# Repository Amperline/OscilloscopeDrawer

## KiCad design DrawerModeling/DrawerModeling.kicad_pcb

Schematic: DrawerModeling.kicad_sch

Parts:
B1_a1, B1_a2, B1_b1, B1_b2, B2_a1, B2_a2, B2_b1, B2_b2: Conn_01x01; SolderWirePad_1x01_SMD_1.5x3mm
C1, C2, C3, C5, C6, C7, C10, C13, C14: C; C_Axial_L3.8mm_D2.6mm_P7.50mm_Horizontal
C4: C_Polarized; CP_Radial_D6.3mm_P2.50mm; not fitted
C_G1, C_G2: C; C_0603_1608Metric
C_s1, C_s3, C_s4, C_s8: 100n; C_0603_1608Metric
C_s5, C_s6: 1u; C_0603_1608Metric
C_s7: C; C_0603_1608Metric
ConnProgramator1: Conn_01x04_Pin; PinHeader_1x04_P2.54mm_Vertical
D1: 1N4148; D_DO-35_SOD27_P7.62mm_Horizontal
D5, D6: LED; LED_D5.0mm
J1: Conn_01x05_Pin; PinHeader_1x05_P2.54mm_Vertical
Q1, Q2, Q4, Q5: 2N3904; TO-92_Inline
Q3: 2N3906; TO-92_Inline
R1, R2: 4.7k; R_Axial_DIN0207_L6.3mm_D2.5mm_P10.16mm_Horizontal
R3, R4, R5, R6, R7, R8, R9, R10, R11, R13, R14, R15, R16, R17, R19, R20, R21, R22, R23, R24, R25, R26, R27, R28, R29, R30, R31, R32, R33, R34, R35, R36, R37, R38, R39, R40, R41, R42, R43, R44, R45, R46: R; R_Axial_DIN0207_L6.3mm_D2.5mm_P10.16mm_Horizontal
R18: R_Potentiometer_US; Potentiometer_Alps_RK163_Single_Horizontal
R60: 10k; R_Axial_DIN0207_L6.3mm_D2.5mm_P10.16mm_Horizontal
U1: AD633JRZ-R7; SOIC127P600X175-8N; MPN AD633JRZ-R7; not fitted
U2, U6, U9, U10, U13, U15: TL072; DIP-8_W10.16mm
U3: Arduino_LCD_Shield
U4: TL082_Block; DIP-8_W7.62mm; not fitted
U5: PinHeader_1x20_P2.54mm_Vertical; not fitted
U7: STM32F401CCUx; QFN-48-1EP_7x7mm_P0.5mm_EP5.6x5.6mm
U8, U20: LT1011; SOIC-8_3.9x4.9mm_P1.27mm
U11, U12, U16, U17: TLP222A; TLP127
U14: LM13700; DIP-16_W7.62mm
U18: MCP4725xxx-xCH; SOT-23-6
U19: XC6206PxxxMR; SOT-23-3
UART1: Conn_01x03_Pin; PinHeader_1x03_P2.54mm_Vertical
V3: VPWL; not fitted
Vw_GND1: Conn_01x01; SolderWirePad_1x01_SMD_1.5x3mm
Vw_MC1: Conn_01x01; SolderWirePad_1x01_SMD_1.5x3mm
Vw_Mdltn1: Conn_01x01; SolderWirePad_1x01_SMD_1.5x3mm
Vw_Out1: Conn_01x01; SolderWirePad_1x01_SMD_1.5x3mm
Vw_PWM1: Conn_01x01; SolderWirePad_1x01_SMD_1.5x3mm
Vw_SIN1: Conn_01x01; SolderWirePad_1x01_SMD_1.5x3mm
Vw_SIN+Cnst1: Conn_01x01; SolderWirePad_1x01_SMD_1.5x3mm
Vw_long1: Conn_01x01; SolderWirePad_1x01_SMD_1.5x3mm
Vw_short1: Conn_01x01; SolderWirePad_1x01_SMD_1.5x3mm
Y1: Crystal; Crystal_HC49-U_Vertical

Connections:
/3V3: C_s1.1, C_s3.1, C_s4.1, C_s6.2, ConnProgramator1.4, R33.2, U7.1 (VBAT), U7.9 (VREF+), U7.24 (VDD), U7.36 (VDD), U7.48 (VDD), U19.2 (VO), U20.8 (V+)
/LCD_CS: U3.25 (LCD_CS), U7.19 (PB1)
/LCD_DC: U3.22 (LCD_DS), U7.18 (PB0)
/MISO: U3.27 (MISO), U7.16 (PA6)
/MOSI: U3.26 (MOSI), U7.17 (PA7)
/PWM: Q1.2 (B), R41.1, R42.2, U7.10 (PA0), Vw_PWM1.1
/RX: U7.31 (PA10), UART1.2
/SCL: R1.2, U7.42 (PB6), U18.5 (SCL)
/SCLK: U3.28 (SCLK), U7.15 (PA5)
/SDA: R2.2, U7.43 (PB7), U18.4 (SDA)
/SD_CS: U3.20 (SD_CS), U7.40 (PB4)
/SWCLK: ConnProgramator1.2, U7.37 (PA14)
/SWDIO: ConnProgramator1.3, U7.34 (PA13)
/Signal_drwng: U10.5 (+), U18.1 (VOUT)
/TP_CS: U3.19 (TP_CS), U7.20 (PB2)
/TP_IRQ: U3.18 (TP_IRQ), U7.25 (PB12)
/TX: U7.30 (PA9), UART1.1
/V5: C_s5.2, J1.2, Q2.3 (C), R1.1, R2.1, R26.2, U3.5 (+5V), U3.24 (LCD_BL), U18.3 (VDD), U19.3 (VI)
/V5m: J1.4
/V15: C2.1, C14.1, J1.1, Q4.3 (C), R13.2, R25.2, R35.1, R40.2, R41.2, R44.1, U2.8 (V+), U6.8 (V+), U8.8 (V+), U9.8 (V+), U10.8 (V+), U13.8 (V+), U14.11 (V+), U15.8 (V+)
/V15m: B2_a1.1, B2_a2.1, J1.5, R23.1, U2.4 (V-), U6.4 (V-), U8.4 (V-), U9.4 (V-), U10.4 (V-), U13.4 (V-), U14.6 (V-), U15.4 (V-)
GND: C1.2, C2.2, C3.2, C5.1, C13.2, C14.2, C_G1.1, C_G2.1, C_s1.2, C_s3.2, C_s4.2, C_s5.1, C_s6.1, C_s7.1, C_s8.2, ConnProgramator1.1, J1.3, R6.1, R9.2, R10.1, R16.2, R28.1, R34.2, R36.1, R39.1, R42.1, R43.2, R45.2, R46.1, R60.1, U3.6 (GND), U7.8 (VSSA), U7.23 (VSS), U7.35 (VSS), U7.47 (VSS), U7.49 (VSS), U8.1 (GND), U8.2 (+), U9.3 (+), U11.2, U11.3, U12.2, U13.3 (+), U13.5 (+), U14.3 (+), U15.5 (+), U18.2 (VSS), U19.1 (GND), U20.1 (GND), U20.2 (+), U20.4 (V-), UART1.3, Vw_GND1.1
unnamed: B1_a1.1, D1.1 (K)
unnamed: B1_a2.1, U10.1, U10.2 (-)
unnamed: B1_b1.1, R15.2, R18.1, U11.4
unnamed: B1_b2.1, R19.2, R20.2, U12.4
unnamed: B2_b1.1, D6.1 (K), U17.2
unnamed: B2_b2.1, D5.1 (K), U16.2
unnamed: C7.1, R8.1
unnamed: D1.2 (A), U9.6 (-), U9.7
unnamed: D5.2 (A), D6.2 (A), R9.1
unnamed: Q1.3 (C), R40.1
unnamed: Q1.1 (E), R7.1, R39.2
unnamed: Q2.2 (B), R19.1
unnamed: Q2.1 (E), R21.1
unnamed: Q3.2 (B), R15.1, R20.1
unnamed: Q3.3 (C), R27.1
unnamed: Q3.1 (E), R26.1, R28.2
unnamed: C5.2, Q4.2 (B), R18.2, U12.3
unnamed: Q4.1 (E), Q5.2 (B), R34.1, R35.2, R45.1
unnamed: Q5.3 (C), R44.2
unnamed: Q5.1 (E), R29.1, R43.1
unnamed: R11.2, R24.1, U14.16
unnamed: R16.1, U16.1, U17.1
unnamed: R21.2, U12.1
unnamed: R22.2, U15.7, U16.4
unnamed: R27.2, U11.1
unnamed: R30.2, R31.1, U13.1
unnamed: R37.1, R38.2, U2.1
unnamed: U1.5 (W), U1.6 (+VS)
unnamed: C3.1, R7.2, U2.3 (+)
unnamed: R36.2, R38.1, U2.2 (-)
unnamed: C13.1, R37.2, U2.5 (+)
unnamed: R5.1, U2.6 (-), U2.7
unnamed: U5.B2, V3.1
unnamed: U5.GND, V3.2
unnamed: C1.1, R5.2, U6.3 (+)
unnamed: C6.1, U6.1, U6.2 (-), Vw_SIN+Cnst1.1
unnamed: R8.2, U6.6 (-), U6.7
unnamed: R60.2, U7.44 (BOOT0)
unnamed: C_s8.1, U7.7 (NRST)
unnamed: R33.1, R46.2, U7.13 (PA3), U20.7
unnamed: C_G1.2, U7.5 (PH0), Y1.2
unnamed: C_G2.2, U7.6 (PH1), Y1.1
unnamed: C_s7.2, U7.22 (VCAP1)
unnamed: C7.2, C10.1, R14.2, U9.2 (-)
unnamed: C10.2, R14.1, U9.1, U9.5 (+), Vw_short1.1
unnamed: R6.2, R13.1, U6.5 (+), U8.7, U10.3 (+), Vw_long1.1
unnamed: R4.1, R11.1, U10.6 (-), U10.7, Vw_MC1.1
unnamed: R29.2, R30.1, U13.2 (-)
unnamed: R31.2, R32.1, U13.6 (-)
unnamed: U14.10, U14.12
unnamed: R3.1, U14.14 (+)
unnamed: R3.2, R4.2, U14.13 (-)
unnamed: R25.1, U14.15 (DIODE_BIAS)
unnamed: U14.4 (-), U14.5
unnamed: R17.1, R23.2, U14.9, U15.3 (+)
unnamed: U15.1, U15.2 (-), U17.4
unnamed: R17.2, R22.1, U15.6 (-)
unnamed: C6.2, R10.2, U8.3 (-), U20.3 (-), Vw_SIN1.1
unnamed: R24.2, R32.2, U13.7, Vw_Mdltn1.1
unnamed: U16.3, U17.3, Vw_Out1.1

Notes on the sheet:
27pF

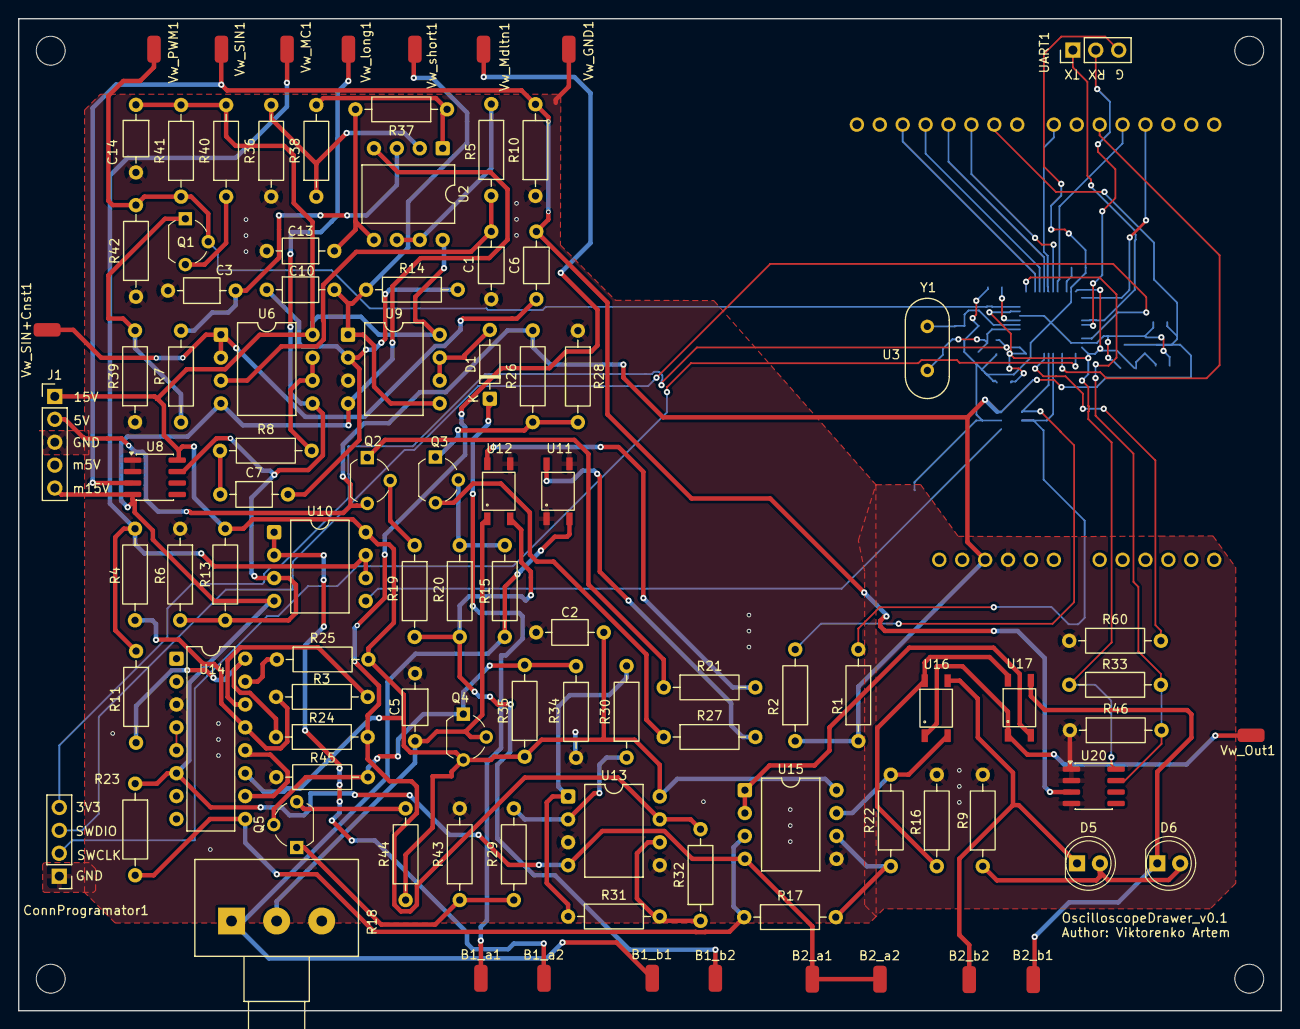
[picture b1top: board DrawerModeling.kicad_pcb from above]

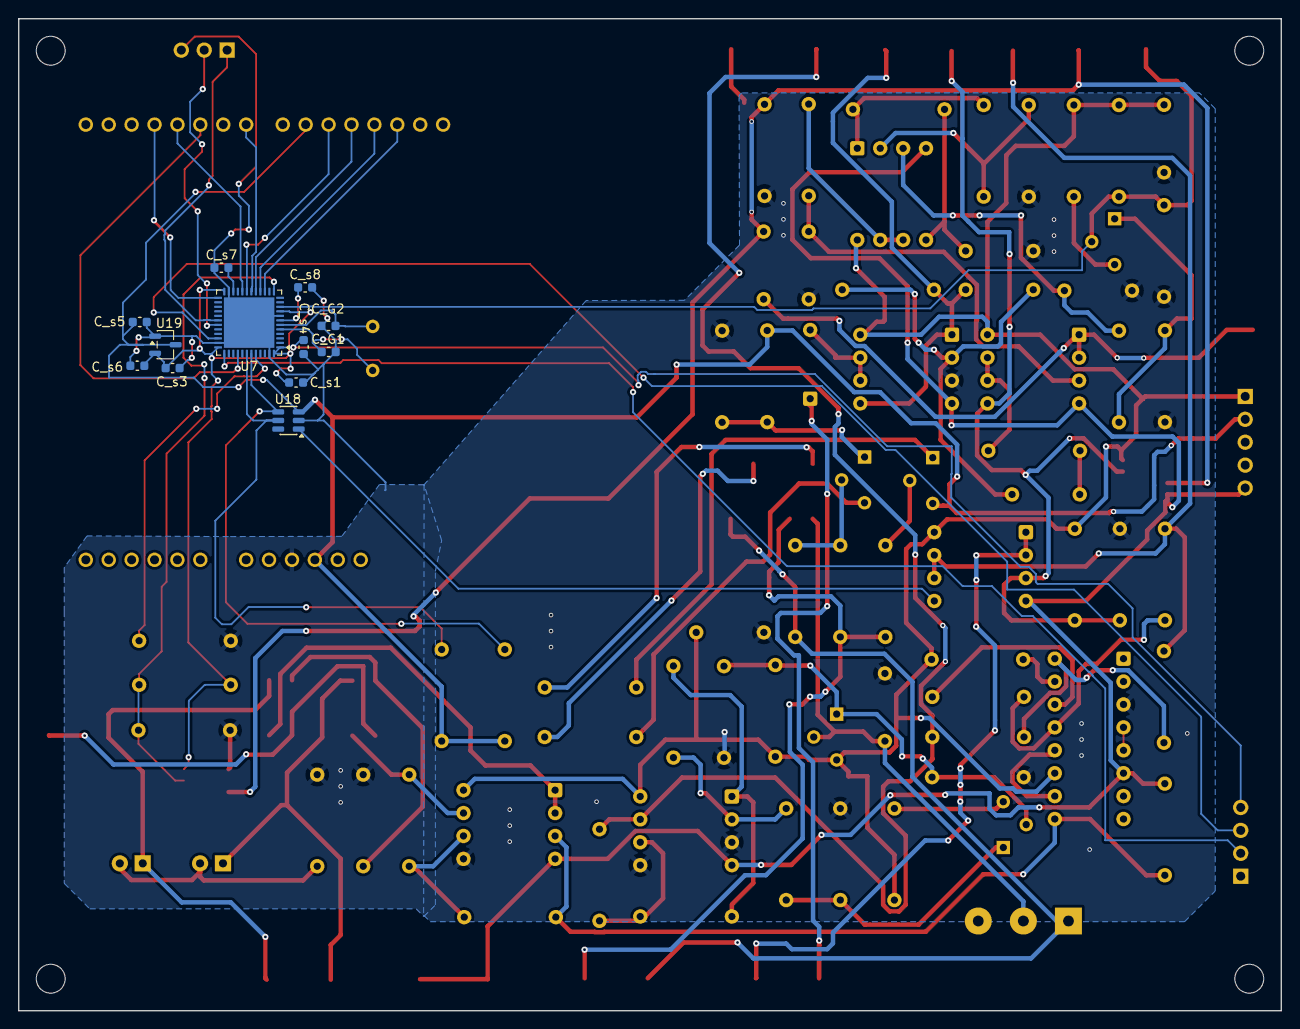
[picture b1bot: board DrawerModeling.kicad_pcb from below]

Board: 2 copper layers, 140.0 x 110.0 mm, 110 parts (12 on the bottom side), 78 nets.

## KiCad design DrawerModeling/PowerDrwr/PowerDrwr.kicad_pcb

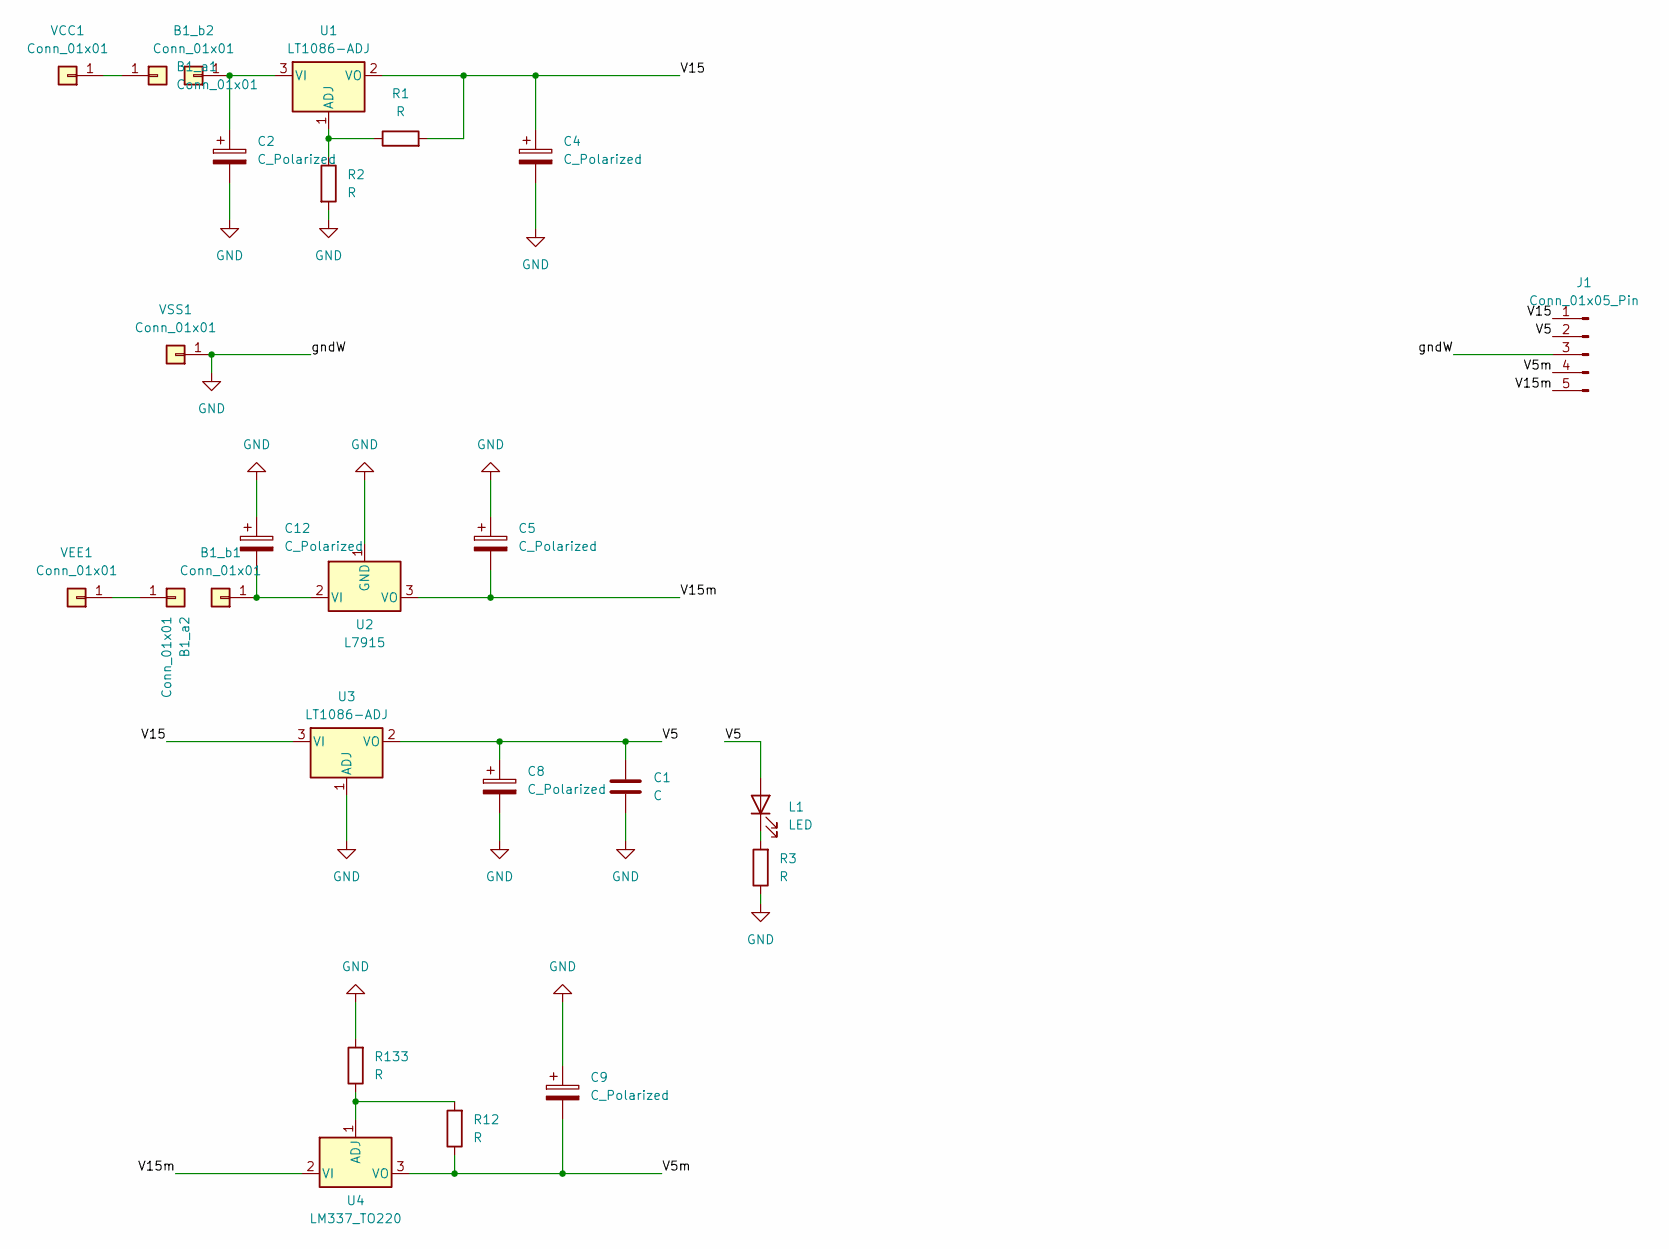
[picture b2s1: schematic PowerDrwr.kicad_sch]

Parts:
B1_a1, B1_a2, B1_b1, B1_b2: Conn_01x01; SolderWirePad_1x01_SMD_1.5x3mm
C1: C; C_Axial_L3.8mm_D2.6mm_P7.50mm_Horizontal
C2, C4, C5, C12: C_Polarized; CP_Radial_D6.3mm_P2.50mm
C8, C9: C_Polarized; CP_Radial_D4.0mm_P1.50mm
J1: Conn_01x05_Pin; PinHeader_1x05_P2.54mm_Vertical
L1: LED; LED_D5.0mm
R1, R2, R3, R12, R133: R; R_Axial_DIN0207_L6.3mm_D2.5mm_P10.16mm_Horizontal
U1, U3: LT1086-ADJ; TO-220-3_Vertical
U2: L7915; TO-220-3_Vertical
U4: LM337_TO220; TO-220-3_Vertical
VCC1: Conn_01x01; SolderWirePad_1x01_SMD_1.5x3mm
VEE1: Conn_01x01; SolderWirePad_1x01_SMD_1.5x3mm
VSS1: Conn_01x01; SolderWirePad_1x01_SMD_1.5x3mm

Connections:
/V5: C1.1, C8.1, J1.2, L1.2 (A), U3.2 (VO)
/V5m: C9.2, J1.4, R12.1, U4.3 (VO)
/V15: C4.1, J1.1, R1.2, U1.2 (VO), U3.3 (VI)
/V15m: C5.2, J1.5, U2.3 (VO), U4.2 (VI)
GND: C1.2, C2.2, C4.2, C5.1, C8.2, C9.1, C12.1, J1.3, R2.2, R3.1, R133.2, U2.1 (GND), U3.1 (ADJ), VSS1.1
unnamed: B1_a1.1, VCC1.1
unnamed: B1_a2.1, VEE1.1
unnamed: B1_b1.1, C12.2, U2.2 (VI)
unnamed: B1_b2.1, C2.1, U1.3 (VI)
unnamed: L1.1 (K), R3.2
unnamed: R1.1, R2.1, U1.1 (ADJ)
unnamed: R12.2, R133.1, U4.1 (ADJ)

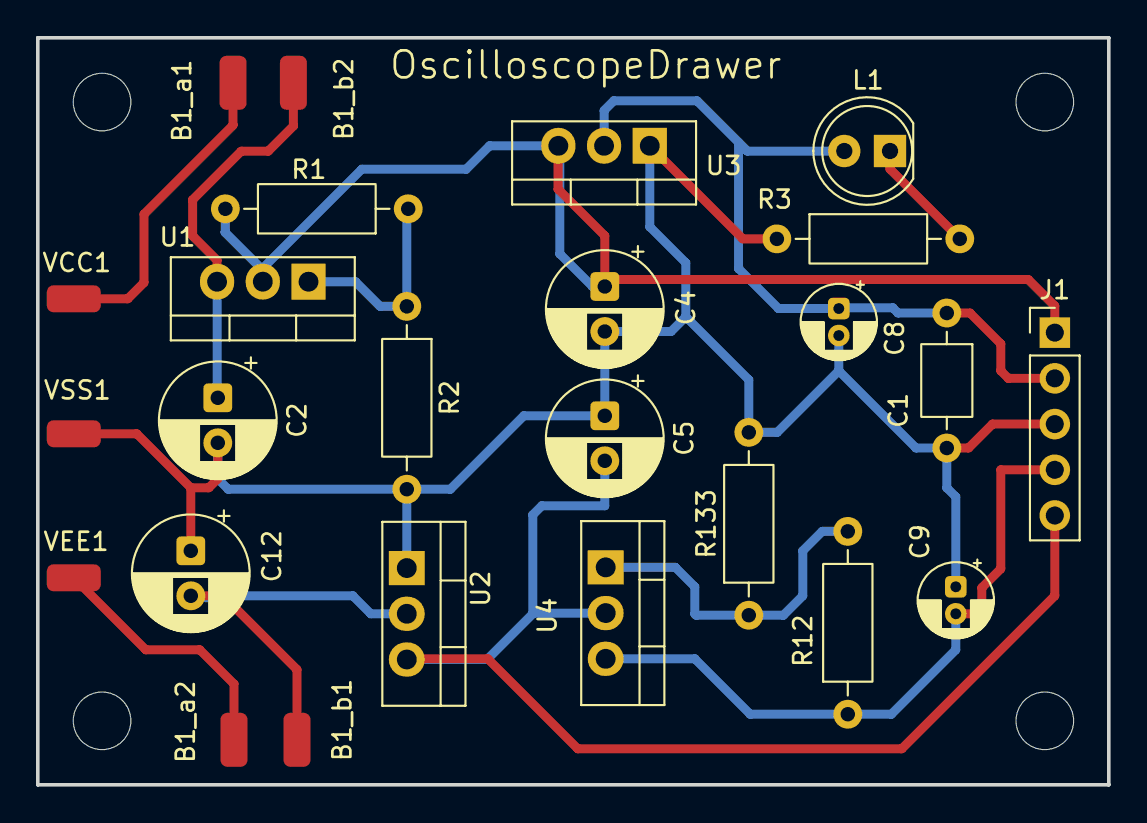
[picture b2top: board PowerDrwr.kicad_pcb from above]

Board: 2 copper layers, 59.5 x 41.5 mm, 25 parts (0 on the bottom side), 12 nets.

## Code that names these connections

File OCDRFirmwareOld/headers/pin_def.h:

#ifndef PIN_DEF
#define PIN_DEF

#include <avr/io.h>
#define F_CPU 8000000U

// SCLK	SPI clock
// MISO	SPI master in slave out
// MOSI	SPI master out slave in
// LCD_CS	LCD chip select signal
// LCD_BL	LCD backlight control signal
// LCD_DC	LCD digital command signal
// SD_CS	SD chip select signal
// TP_CS	XPT2046 chip select signal
// TP_IRQ	XPT2046 interrupt output signal

//PORT A
#define PA0           PA0
#define PA1           PA1
#define PA2           PA2
#define PA3           PA3
#define PA5           PA5
#define PA5           PA5
#define PA6           PA6
#define PA7           PA7

//PORT B
#define PB0           PB0
#define PB1           PB1
#define _PIN_SD_CS    (1<<PB2)
#define _PIN_TP_CS    (1<<PB3)
#define _PIN_LCD_CS   (1<<PB4) //(=1 always)
#define _PIN_MOSI     (1<<PB5)
#define _PIN_MISO     (1<<PB6)
#define _PIN_SCLK     (1<<PB7)

//PORT C
#define PC0           PC0
#define PC1           PC1
#define PC2           PC2
#define PC3           PC3
#define PC5           PC5
#define PC5           PC5
#define PC6           PC6
#define PC7           PC7

//PORT D
#define PD0           (1<<PD0)
#define PD1           PD1
#define _PIN_TP_IRQ   (1<<PD2)
#define PD3           PD3
#define _PIN_LCD_DC   (1<<PD4)
#define PD5           PD5
#define _PIN_LCD_BL   (1<<PD6)
#define PD7           PD7




//MASKs for chip select
#define CS_MASK_LCD ~(_PIN_LCD_CS)
#define CS_MASK_TP ~(_PIN_TP_CS)

#define CS_CLEAR_ALL (_PIN_LCD_CS | _PIN_SD_CS | _PIN_TP_CS)

//sclk 8 MHz
//MASKs for SPI
#define SPI_control_BASIC_MASK ((1<<SPIE) | (1<<SPE) | (1<<MSTR))
#define SPI_control_LCD_MASK (SPI_control_BASIC_MASK)
#define SPI_control_TP_MASK (SPI_control_BASIC_MASK | (1<<SPR0))

#define SPI_status_BASIC_MASK 0x01


#endif

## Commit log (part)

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2026-01-10 edit_0
2026-01-13 edit_1 scheme first success
2026-01-14 edit_2 still developing scheme
2026-01-14 edit_3 added tl082 block
2026-01-17 edit_4 Scheme logic is completed
2026-01-18 edit_5 Significant errors fixed
2026-01-18 edit_5 All for today
2026-01-20 edit_6 counting [200~
2026-01-21 edit_7 testing simulation(1)
2026-01-23 edit_7 it becomes tricky
2026-04-04 going to lin
2026-04-07 first linux commit
2026-06-06 pcb_1
